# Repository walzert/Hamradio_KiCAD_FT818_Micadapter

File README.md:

# Hamradio_KiCAD_FT818_Micadapter

A simple Y-splitter for the RJ45 microfon plug of the FT818 should work with same pinout.
It routes 1:1 and breaks the pins out in pair with ground. 

The adpater could be used to connect a XLR microfon and buttons instead of the original MH31 mic. It also could be used for connecting a mircocontroller to that and build 
something like the MH-36E8J, deeper research for the commands is important.

Routing could be changed / extended add don't care about the FST/DWN/UP buttons and rout audio over CAT5 cable.

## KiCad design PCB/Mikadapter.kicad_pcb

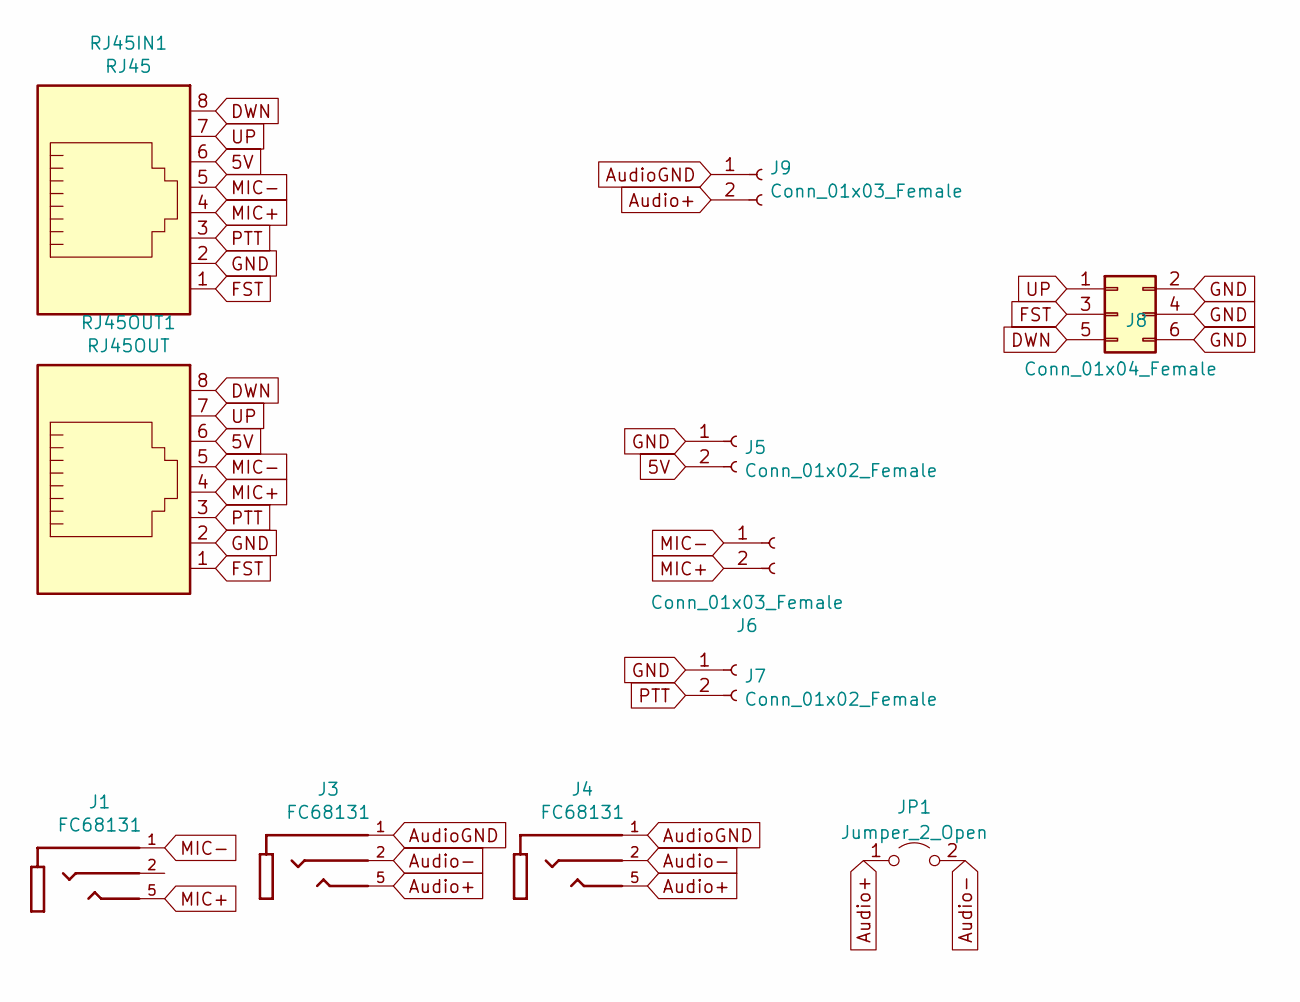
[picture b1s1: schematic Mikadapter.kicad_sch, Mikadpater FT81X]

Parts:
J1, J3, J4: FC68131; CLIFF_FC68131; PARTREV 5
J5, J7: Conn_01x02_Female; PinHeader_1x02_P2.54mm_Vertical
J6, J9: Conn_01x03_Female; PinHeader_1x02_P2.54mm_Vertical
J8: Conn_01x04_Female; PinHeader_2x03_P2.54mm_Vertical
JP1: Jumper_2_Open; SolderJumper-2_P1.3mm_Open_TrianglePad1.0x1.5mm
RJ45IN1: RJ45; RJ45_Wuerth_7499010001A_Horizontal
RJ45OUT1: RJ45OUT; RJ45_Wuerth_7499010001A_Horizontal

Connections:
5V: J5.2, RJ45IN1.6, RJ45OUT1.6
Audio+: J3.5, J4.5, J9.2, JP1.1 (A)
Audio-: J3.2, J4.2, JP1.2 (B)
AudioGND: J3.1, J4.1, J9.1
DWN: J8.5, RJ45IN1.8, RJ45OUT1.8
FST: J8.3, RJ45IN1.1, RJ45OUT1.1
GND: J5.1, J7.1, J8.2, J8.4, J8.6, RJ45IN1.2, RJ45OUT1.2
MIC+: J1.5, J6.2, RJ45IN1.4, RJ45OUT1.4
MIC-: J1.1, J6.1, RJ45IN1.5, RJ45OUT1.5
PTT: J7.2, RJ45IN1.3, RJ45OUT1.3
UP: J8.1, RJ45IN1.7, RJ45OUT1.7

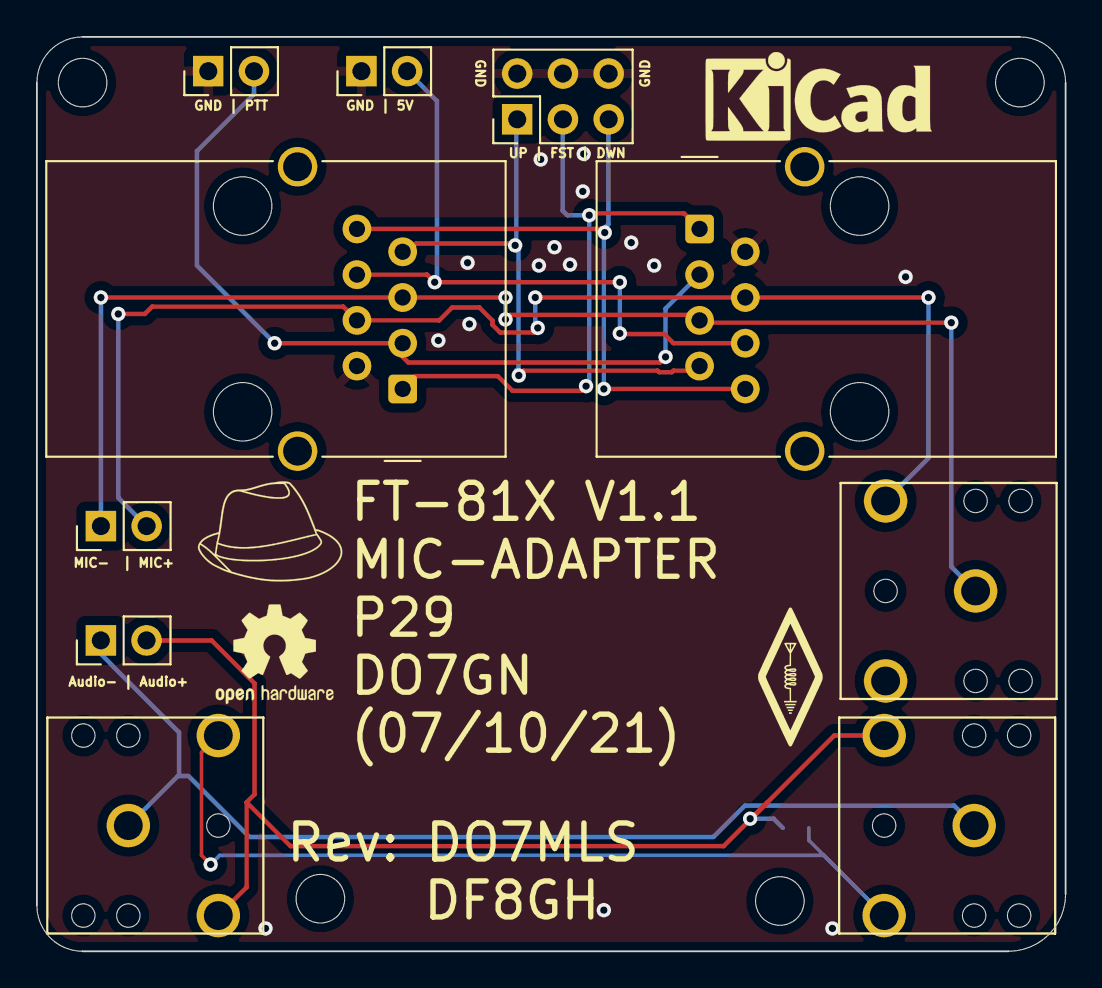
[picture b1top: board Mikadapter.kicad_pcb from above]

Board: 2 copper layers, 57.1 x 50.8 mm, 12 parts (1 on the bottom side), 11 nets.

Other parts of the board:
e: OSHW-Logo2_7.3x6mm_SilkScreen

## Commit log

2021-04-09 Upload V1
2021-04-09 Update Readme
    Update Readme
2021-04-09 changed width of 5V trace and pinout on the sides
2021-04-09 changed layout for FST|DWN|UP buttons
2021-09-30 transformed in KiCAD 6 and changed layout and changed pinout for RJ45
2021-09-30 added schema as PDF and changed schema informations
2021-10-01 changed name to ft-81x
2021-10-07 Changed Audio pins after inspection of the jack
2022-06-06 Added trace for second Audio channel, new folder, 3D
2022-06-06 Updated PCB Image
